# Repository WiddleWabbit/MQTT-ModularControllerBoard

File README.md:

# MQTT Modular Controller Board

*Currently In Testing - Not Yet Tested*

ESP32-S3-WROOM-1U based motherboard designed to communicate externally via MQTT, and read sensors, control interfaces and other hardware through purpose built modules. For example, actuator control (pumps, solenoids, etc.), and water sensor readings etc.

## Features

- ESP32-S3-WROOM-1U microcontroller with antenna support
- Four module slots using standardized 2x10 pin headers
- Power rails: 12 V, 5 V, and 3.3 V supplied to modules
- High-side reverse polarity protection on 12 V and 5 V inputs
- USB-powered operation for programming and testing (no 12 V required)
- Screw terminal power input
- 4-layer PCB designed for assembly (routing / GND / GND / routing)
- 4 x 3.5mm Mounting Holes

## Architecture

### Core Components
- **Microcontroller**: ESP32-S3-WROOM-1U
- **Power Input**: 12 V via screw terminals
- **Power Conversion**:
  - 12 V → 5 V using TPS563200DDCR (TI WEBENCH design)
  - 5 V → 3.3 V using LDO
- **Maximum Outputs**:
  - 12 V: Limited by external supply
  - 5 V: 3 A total (0.8 A used internally)
  - 3.3 V: 1 A total (0.6 A used by ESP32)

### Module Interface
Each of the four modules connects via two 10-pin headers and receives:
- Power: 12 V (4 pins shared), 5 V (2 pins), 3.3 V (2 pins), GND (4 pins)
- Communication:
  - Shared SPI: CS(per module), MOSI(GPIO11), MISO(GPIO13), SCK(GPIO12)
  - Shared I²C: SDA(GPIO4), SCL(GPIO5)
- Control/Detection:
  - One general-purpose GPIO per module
  - One module detection/sense pin per module
  - Module-specific CS pins.

#### Module Slots (Left to Right)
Slot 1:
- General Purpose: GPIO1
- Module Detection: GPIO2
- CS Pin: GPIO16
  
Slot 2:
- General Purpose: GPIO43
- Module Detection: GPIO44
- CS Pin: GPIO15
  
Slot 3:
- General Purpose: GPIO42
- Module Detection: GPIO41
- CS Pin: GPIO7
  
Slot 4:
- General Purpose: GPIO40
- Module Detection: GPIO39
- CS Pin: GPIO6
  
### Additional Features
- USB micro-B for programming and power (VBUS sense on GPIO08)
- Power indicator LED on 3.3 V rail
- EN button and RESET functionality
- Manual download mode: Hold BOOT button while pressing RESET, then release BOOT

### PCB Stackup
4-layer board:  
Component/Routing → Ground plane → Ground plane → Routing

Impedance Control:
Designed for JLCPCB Impedance Control Stackup of JLC04161H-7628, Finished thickness of 1.59mm.

## Setup and Build

**Firmware**: The PlatformIO firmware includes non-blocking WiFi station
reconnection and a captive-portal setup flow. On first boot, the portal scans
nearby networks and offers a selectable SSID list plus manual SSID entry.

**Programming**:
- Connect via USB micro-B.
- Use ESP32 flashing tools (esptool, Arduino IDE, ESP-IDF, etc.).
- For manual bootloader mode: Hold BOOT button, press RESET, release BOOT.

**Module Development**:
Modules must conform to the 2x10 header pinout with 40mm pitch.
Board uses 2 x 10, 8.5mm Female Headers (A2541HWV-10P). Recommended 3A support.

## Repository Contents

- KiCad schematic and PCB files
- Project configuration
- Backups folder

## License

This documentation is part of MQTT-ModularControllerBoard Project and is licensed under the CERN Open Hardware Licence Version 2 - Permissive (CERN-OHL-P-2.0). 
You may redistribute and modify this documentation under the terms of the CERN-OHL-P-2.0. 
This documentation is distributed WITHOUT ANY EXPRESS OR IMPLIED WARRANTY, INCLUDING OF MERCHANTABILITY, SATISFACTORY QUALITY AND FITNESS FOR A PARTICULAR PURPOSE. See the CERN-OHL-P-2.0 for applicable conditions.

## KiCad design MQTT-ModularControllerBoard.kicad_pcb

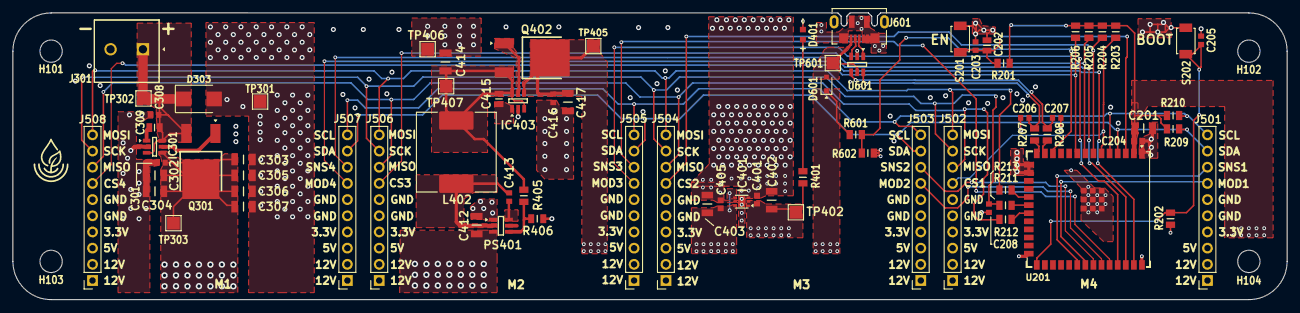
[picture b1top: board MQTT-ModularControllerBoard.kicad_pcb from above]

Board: 4 copper layers, 200.0 x 45.0 mm, 81 parts (0 on the bottom side), 44 nets.

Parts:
C201, C302, C303, C304, C305, C306, C307, C402, C405, C412, C417: 10uF 10% 25V; CAPC3216X180N
C202: 1uF 10% 50V; CAPC2012X135N
C203, C204, C205, C301, C308, C401, C403, C413, C416: 0.1uF 10% 50V; CAPC1608X90N
C206, C207, C208: 22pF 5% 50V; CAPC1608X90N
C309, C415: 220nF 10% 50V; CAPC2012X135N
C414: 47uF 20% 10V; CAPC3216X190N
D303: 13V 21.5V 1uA Leak; DO-214AA_Bidirectional
D401: KT-0603R; LED_0603_1608Metric
D601: 40V 1A; D_SOD-323F
H101, H102, H103, H104: 3.5mm; MountingHole_3.5mm
IC301, IC403: LM74700QDBVTQ1; SOT95P280X145-6N
IC401: TLV76733DRVR; SON65P200X200X80-7N
J301: 1715721
J501, J502, J503, J504, J505, J506, J507, J508: A2541HWV-10P; PinSocket_1x10_P2.54mm_Vertical_Female
J601: 1051640001; CON00906_5_MOL
L402: 10uH, 5.4A, 20%; L_SXN_SMDRI127
PS401: TPS54308DDCR; SOT95P280X110-6N
Q301, Q402: 60V 38A; DPAK__SINGLE-GAUGE__TO-252_369C__ISSUE_F
R201, R202, R203, R204, R205, R206: 10kΩ 1/8W 1%; RESC2013X65N
R207, R208: 22Ω 1/8W 5%; RESC2013X65N
R209, R210: 4.7kΩ 1/8W 1%; RESC2013X65N
R211, R212, R213: 47Ω 1/8W 1%; RESC2013X65N
R401: 330Ω 1/8W 1%; RESC2013X65N
R405, R601, R602: 100kΩ 1/8W 1%; RESC2013X65N
R406: 13.7kΩ 1/8W 1%; RESC2012X60N
S201, S202: Push Button SPST; SW_TS-1088-AR02016
TP301, TP302, TP303, TP402, TP405, TP406, TP407, TP601: TestPoint; TestPoint_Pad_2.0x2.0mm
U201: ESP32-S3-WROOM-1U-N16R8; ESP32-S3-WROOM-1U
U601: ESD Protection IC; SOT95P280X145-6N

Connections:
+3V3: C201.2, C204.1, C401.1, C402.2, IC401.1 (OUT), IC401.2 (SNS), J501.4, J502.4, J503.4, J504.4, J505.4, J506.4, J507.4, J508.4, R201.1, R202.2, R203.2, R204.2, R205.2, R206.2, R209.2, R210.2, R401.2, TP402.1, U201.2 (3V3)
+5V: C403.1, C405.2, C416.2, C417.2, D601.1 (K), IC401.4 (EN), IC401.6 (IN), IC403.4 (CATHODE), J501.3, J502.3, J503.3, J504.3, J505.3, J506.3, J507.3, J508.3, Q402.2 (D), R601.1, TP405.1
+12V: C301.2, C302.2, C303.2, C304.2, C305.2, C306.2, C307.2, C412.2, IC301.4 (CATHODE), J501.1, J501.2, J502.1, J502.2, J503.1, J503.2, J504.1, J504.2, J505.1, J505.2, J506.1, J506.2, J507.1, J507.2, J508.1, J508.2, PS401.3 (VIN), Q301.2 (D), TP303.1
/ESP32-S3/BOOT: C205.1, R202.1, S202.1, U201.27 (GPIO0/BOOT)
/ESP32-S3/CS1: J502.7, R203.1, U201.6 (GPIO6/TOUCH6/ADC1_CH5)
/ESP32-S3/CS2: J504.7, R204.1, U201.7 (GPIO7/TOUCH7/ADC1_CH6)
/ESP32-S3/CS3: J506.7, R205.1, U201.8 (GPIO15/U0RTS/ADC2_CH4/XTAL_32K_P)
/ESP32-S3/CS4: J508.7, R206.1, U201.9 (GPIO16/U0CTS/ADC2_CH5/XTAL_32K_N)
/ESP32-S3/D+: R207.1, U201.14 (GPIO20/U1CTS/ADC2_CH9/CLK_OUT1/USB_D+)
/ESP32-S3/D-: R208.1, U201.13 (GPIO19/U1RTS/ADC2_CH8/CLK_OUT2/USB_D-)
/ESP32-S3/D_R+: C206.2, R207.2, U601.6 (I/O1)
/ESP32-S3/D_R-: C207.2, R208.2, U601.4 (I/O2)
/ESP32-S3/EN: C202.2, C203.1, R201.2, S201.1, U201.3 (EN)
/ESP32-S3/MISO: R212.1, U201.21 (GPIO13/TOUCH13/ADC2_CH2/FSPIQ/FSPIIO7/S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)
/ESP32-S3/MISO_R: J502.8, J504.8, J506.8, J508.8, R212.2
/ESP32-S3/MOD1: J501.7, U201.33 (MTDO/GPIO40/CLK_OUT2)
/ESP32-S3/MOD2: J503.7, U201.35 (MTMS/GPIO42)
/ESP32-S3/MOD3: J505.7, U201.37 (U0TXD/GPIO43/CLK_OUT1)
/ESP32-S3/MOD4: J507.7, U201.39 (GPIO1/TOUCH1/ADC1_CH0)
/ESP32-S3/MOSI: R211.1, U201.19 (GPIO11/TOUCH11/ADC2_CH0/FSPID/FSPIIO5/S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)
/ESP32-S3/MOSI_R: J502.10, J504.10, J506.10, J508.10, R211.2
/ESP32-S3/SCK: R213.1, U201.20 (GPIO12/TOUCH12/ADC2_CH1/FSPICLK/FSPIIO6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)
/ESP32-S3/SCK_R: C208.1, J502.9, J504.9, J506.9, J508.9, R213.2
/ESP32-S3/SCL: J501.10, J503.10, J505.10, J507.10, R210.1, U201.5 (GPIO5/TOUCH5/ADC1_CH4)
/ESP32-S3/SDA: J501.9, J503.9, J505.9, J507.9, R209.1, U201.4 (GPIO4/TOUCH4/ADC1_CH3)
/ESP32-S3/SENSE1: J501.8, U201.32 (MTCK/GPIO39/CLK_OUT3/SUBSPICS1)
/ESP32-S3/SENSE2: J503.8, U201.34 (MTDI/GPIO41/CLK_OUT1)
/ESP32-S3/SENSE3: J505.8, U201.36 (U0RXD/GPIO44/CLK_OUT2)
/ESP32-S3/SENSE4: J507.8, U201.38 (GPIO2/TOUCH2/ADC1_CH1)
/ESP32-S3/VBUS_SNS: R601.2, R602.1, U201.12 (GPIO8/TOUCH8/ADC1_CH7/SUBSPICS1)
/USB Input/D+: J601.3 (D+), U601.1 (I/O1)
/USB Input/D-: J601.2 (D-), U601.3 (I/O2)
GND: C201.1, C202.1, C203.2, C204.2, C205.2, C206.1, C207.1, C208.2, C301.1, C302.1, C303.1, C304.1, C305.1, C306.1, C307.1, C308.2, C401.2, C402.1, C403.2, C405.1, C412.1, C414.1, C416.1, C417.1, D303.2 (A2), D401.1 (K), IC301.2 (GND), IC401.3 (GND_1), IC401.5 (GND_2), IC401.7 (EP), IC403.2 (GND), J301.2, J501.5, J501.6, J502.5, J502.6, J503.5, J503.6, J504.5, J504.6, J505.5, J505.6, J506.5, J506.6, J507.5, J507.6, J508.5, J508.6, J601.4 (ID), J601.5 (GND), J601.6 (GND), PS401.1 (GND), R406.1, R602.2, S201.2, S202.2, TP301.1, TP406.1, U201.1 (GND), U201.15 (GPIO3/TOUCH3/ADC1_CH2), U201.16 (GPIO46), U201.26 (GPIO45), U201.40 (GND), U201.41 (GND), U601.2 (GND)
unnamed: C308.1, C309.1, D303.1 (A1), IC301.3 (EN), IC301.6 (ANODE), J301.1, Q301.3 (S), TP302.1
unnamed: D401.2 (A), R401.1
unnamed: D601.2 (A), J601.1 (VBUS), TP601.1, U601.5 (VBUS)
unnamed: IC301.5 (GATE), Q301.1 (G)
unnamed: C309.2, IC301.1 (VCAP)
unnamed: C414.2, C415.2, IC403.3 (EN), IC403.6 (ANODE), L402.2, Q402.3 (S), R405.2, TP407.1
unnamed: IC403.5 (GATE), Q402.1 (G)
unnamed: C415.1, IC403.1 (VCAP)
unnamed: C413.2, PS401.6 (BOOT)
unnamed: PS401.4 (FB), R405.1, R406.2
unnamed: C413.1, L402.1, PS401.2 (SW)

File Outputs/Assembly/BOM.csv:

"#","Qty","Reference","Value","Manufacturer","Manufacturer Part No","JLCPCB Part #","Package","Footprint"
"1","11","C201,C302,C303,C304,C305,C306,C307,C402,C405,C412,C417","10uF 10% 25V","Samsung Electro-Mechanics","CL31A106KAHNNNE","C9807","1206","JLCPCB Basic:CAPC3216X180N"
"2","1","C202","1uF 10% 50V","Samsung Electro-Mechanics","CL21B105KBFNNNE","C28323","0805","JLCPCB Basic:CAPC2012X135N"
"3","9","C203,C204,C205,C301,C308,C401,C403,C413,C416","0.1uF 10% 50V","YAGEO","CC0603KRX7R9BB104","C14663","0603","JLCPCB Basic:CAPC1608X90N"
"4","1","C208","22pF 5% 50V","Samsung Electro-Mechanics","CL10C220JB8NNNC","C1653","0603","JLCPCB Basic:CAPC1608X90N"
"5","2","C309,C415","220nF 10% 50V","Samsung Electro-Mechanics","CL21B224KBFNNNE","C5378","0805","JLCPCB Basic:CAPC2012X135N"
"6","1","C414","47uF 20% 10V","Samsung Electro-Mechanics","CL31A476MPHNNNE","C96123","1206","JLCPCB Basic:CAPC3216X190N"
"7","1","D303","13V 21.5V 1uA Leak","Littelfuse","SMBJ13CA","C224008","DO-214AA","LITTELFUSE Diodes:DO-214AA_Bidirectional"
"8","1","D401","KT-0603R","Hubei KENTO Elec"," KT-0603R","C2286","0603","JLCPCB Basic:LED_0603_1608Metric"
"9","1","D601","40V 1A","Guangdong Hottech","1N5819WS","C191023","SOD-323","GUANGDONG HOTTECH Diodes:D_SOD-323F"
"10","2","IC301,IC403","LM74700QDBVTQ1","Texas Instruments","LM74700QDBVTQ1","C2653623","SOT-23-6","TEXAS INSTRUMENTS ICs:SOT95P280X145-6N"
"11","1","IC401","TLV76733DRVR","Texas Instruments","TLV76733DRVR","C2848334","WSON-6(2x2)","TEXAS INSTRUMENTS ICs:SON65P200X200X80-7N"
"12","1","J301","1715721"," Phoenix Contact"," 1715721","C480516","Plugin,P=5.08mm","PHOENIX CONTACT Terminals:1715721"
"13","8","J501,J502,J503,J504,J505,J506,J507,J508","A2541HWV-10P","CJT(Changjiang Connectors)","A2541HWV-10P","C225507","Plugin,P=2.54mm","CJT Connectors:PinSocket_1x10_P2.54mm_Vertical_Female"
"14","1","J601","1051640001","MOLEX","1051640001","C234179","SMD","MOLEX Connectors:CON00906_5_MOL"
"15","1","L402","10uH, 5.4A, 20%","SXN(Shun Xiang Nuo Elec)","SMDRI127-100MT","C9904","SMD,12.3x12.3mm","Inductor_SMD:L_SXN_SMDRI127"
"16","1","PS401","TPS54308DDCR","Texas Instruments","TPS54308DDCR","C168839","SOT-23-6","TEXAS INSTRUMENTS ICs:SOT95P280X110-6N"
"17","2","Q301,Q402","60V 38A","onsemi","NVD5C684NLT4G","C236252","DPAK","ONSEMI Transistors:DPAK__SINGLE-GAUGE__TO-252_369C__ISSUE_F"
"18","6","R201,R202,R203,R204,R205,R206","10kΩ 1/8W 1%","UNI-ROYAL(Uniroyal Elec)","0805W8F1002T5E","C17414","0805","JLCPCB Basic:RESC2013X65N"
"19","2","R207,R208","22Ω 1/8W 5%","UNI-ROYAL(Uniroyal Elec)","0805W8F220JT5E","C17561","0805","JLCPCB Basic:RESC2013X65N"
"20","2","R209,R210","4.7kΩ 1/8W 1%","UNI-ROYAL(Uniroyal Elec)","0805W8F4701T5E"," C17673","0805","JLCPCB Basic:RESC2013X65N"
"21","3","R211,R212,R213","47Ω 1/8W 1%","UNI-ROYAL(Uniroyal Elec)","0805W8F470JT5E","C17714","0805","JLCPCB Basic:RESC2013X65N"
"22","1","R401","330Ω 1/8W 1%","UNI-ROYAL(Uniroyal Elec)","0805W8F3300T5E","C17630","0805","JLCPCB Basic:RESC2013X65N"
"23","3","R405,R601,R602","100kΩ 1/8W 1%","UNI-ROYAL(Uniroyal Elec)","0805W8F1003T5E","C149504","0805","JLCPCB Basic:RESC2013X65N"
"24","1","R406","13.7kΩ 1/8W 1%","YAGEO","AC0805FR-0713K7L","C228298","0805","YAGEO Resistors:RESC2012X60N"
"25","2","S201,S202","Push Button SPST","XUNPU","TS-1088-AR02016","C720477","SMD,4x3mm","JLCPCB Basic:SW_TS-1088-AR02016"
"26","1","U201","ESP32-S3-WROOM-1U-N16R8","Espressif Systems","ESP32-S3-WROOM-1U-N16R8","C3013946","SMD,19.2x18mm","ESPRESSIF Microcontrollers:ESP32-S3-WROOM-1U"
"27","1","U601","ESD Protection IC","STMicroelectronics","USBLC6-2SC6","C7519","SOT-23-6L","STMICROELECTRONICS Protection:SOT95P280X145-6N"

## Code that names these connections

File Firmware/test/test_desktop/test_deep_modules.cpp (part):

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  FakeDigitalPin sns2;
  FakeDigitalPin sns3;
  FakeDigitalPin sns4;
  FakeDigitalPin mod1;
  FakeDigitalPin mod2;
  FakeDigitalPin mod3;
  FakeDigitalPin mod4;
  FakeDigitalPin cs1;
  FakeDigitalPin cs2;
  FakeDigitalPin cs3;
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   */
  explicit SlotRig(FakeClock& clockRef)
    : clock(clockRef),
      pins{{sns1, mod1, cs1},
           {sns2, mod2, cs2},
           {sns3, mod3, cs3},
           {sns4, mod4, cs4}}
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   */
  FakeDigitalPin& mod(uint8_t slotIndex)
  {
    FakeDigitalPin* pinsMod[] = {&mod1, &mod2, &mod3, &mod4};
    return *pinsMod[slotIndex];
  }
};
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  TEST_ASSERT_TRUE(rig.programming.active());
  TEST_ASSERT_EQUAL(PinMode::DigitalOutput, board.slots.cs1.mode);
  TEST_ASSERT_TRUE(board.slots.cs1.level);
  TEST_ASSERT_EQUAL(PinMode::DigitalInput, board.slots.mod1.mode);
  for (int i = 0; i < 3; ++i)
  {
    board.bus.update();
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  board.slots.cs1.setMode(PinMode::DigitalOutput);
  board.slots.cs1.write(true);
  const int cs1Writes = board.slots.cs1.writeCount;
  const int mod3Writes = board.slots.mod3.writeCount;
  const PinMode mod3Mode = board.slots.mod3.mode;
  const int mod1Writes = board.slots.mod1.writeCount;

  ProgrammingRig rig(board, 60000, 1000);
  rig.programming.begin(3, ProgrammingMethod::Isp);
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  Board board(kPollMs, kPollMs, kSolenoidSilenceMs, kPollMs, kPumpSilenceMs);
  board.start();
  ProgrammingRig rig(board, 60000, 1000);
  const int mod1Writes = board.slots.mod1.writeCount;
  const int mod2Writes = board.slots.mod2.writeCount;
  const int mod4Writes = board.slots.mod4.writeCount;
  const PinMode mod1Mode = board.slots.mod1.mode;
  const PinMode mod2Mode = board.slots.mod2.mode;
  const PinMode mod4Mode = board.slots.mod4.mode;
  const int cs1Writes = board.slots.cs1.writeCount;
  const int cs2Writes = board.slots.cs2.writeCount;
  rig.programming.begin(2, ProgrammingMethod::Updi);
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  board.start();
  ProgrammingRig quiet(board, 60000, 1000);
  quiet.port.plugged = false;
  const int mod4Writes = board.slots.mod4.writeCount;
  const PinMode mod4Mode = board.slots.mod4.mode;
  quiet.programming.begin(4, ProgrammingMethod::Updi);
  TEST_ASSERT_EQUAL(PinMode::DigitalInputPullup, quiet.mosi.mode);
  TEST_ASSERT_EQUAL(mod4Mode, board.slots.mod4.mode);
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  TEST_ASSERT_FALSE(rig.programming.updiCheckActive());
  TEST_ASSERT_FALSE(rig.programming.active());
  const int cs3Writes = board.slots.cs3.writeCount;
  const int mod1Writes = board.slots.mod1.writeCount;
  const int mod3Writes = board.slots.mod3.writeCount;
  const PinMode mod1Mode = board.slots.mod1.mode;
  const PinMode mod3Mode = board.slots.mod3.mode;

  TEST_ASSERT_TRUE(rig.programming.startUpdiCheck(3));
  TEST_ASSERT_TRUE(rig.programming.updiCheckActive());
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  ProgrammingRig rig(board, 60000, 1000);
  rig.mosi.externalLevel = false;
  const int cs1Writes = board.slots.cs1.writeCount;
  const int mod1Writes = board.slots.mod1.writeCount;
  const PinMode mod1Mode = board.slots.mod1.mode;
  TEST_ASSERT_TRUE(rig.programming.startUpdiCheck(1));
  TEST_ASSERT_EQUAL(PinMode::DigitalOutputOpenDrain, rig.mosi.mode);
  TEST_ASSERT_FALSE(rig.mosi.level);
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  Board board(kPollMs, kPollMs, kSolenoidSilenceMs, kPollMs, kPumpSilenceMs);
  board.start();
  ProgrammingRig rig(board, 60000, 1000);
  const int mod1Writes = board.slots.mod1.writeCount;
  const int mod2Writes = board.slots.mod2.writeCount;
  const PinMode mod1Mode = board.slots.mod1.mode;
  const PinMode mod2Mode = board.slots.mod2.mode;
  TEST_ASSERT_TRUE(rig.programming.startUpdiCheck(1));
  TEST_ASSERT_EQUAL(PinMode::DigitalOutputOpenDrain, rig.mosi.mode);
  TEST_ASSERT_FALSE(rig.mosi.level);
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  TEST_ASSERT_TRUE(wroteLine(serial, "OK programming"));
  TEST_ASSERT_TRUE(wroteLine(
    serial,
    "ISP slot 1: MOSI GPIO11, MISO GPIO13, SCK GPIO12, RESET GPIO6, 3V3, GND"));

  serial.output.clear();
  serial.feed("program 4 updi\n");
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  TEST_ASSERT_EQUAL(4, request.slot);
  TEST_ASSERT_EQUAL(static_cast<int>(ProgrammingMethod::Updi),
                    static_cast<int>(request.method));
  TEST_ASSERT_TRUE(wroteLine(serial, "UPDI slot 4: UPDI GPIO11, 3V3, GND"));

  serial.output.clear();
  serial.feed("program updi\n");
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
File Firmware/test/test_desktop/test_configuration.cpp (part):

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                    static_cast<int>(request.method));
  TEST_ASSERT_EQUAL_STRING("OK programming", slot1.serial.output[0].c_str());
  TEST_ASSERT_EQUAL_STRING(
    "ISP slot 1: MOSI GPIO11, MISO GPIO13, SCK GPIO12, RESET GPIO6, 3V3, GND",
    slot1.serial.output[1].c_str());

  CommandStack slot2;
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  TEST_ASSERT_TRUE(slot2.controller.takeProgrammingRequest(request));
  TEST_ASSERT_EQUAL(2, request.slot);
  TEST_ASSERT_EQUAL_STRING(
    "ISP slot 2: MOSI GPIO11, MISO GPIO13, SCK GPIO12, RESET GPIO7, 3V3, GND",
    slot2.serial.output[1].c_str());

  CommandStack slot3;
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  TEST_ASSERT_TRUE(slot3.controller.takeProgrammingRequest(request));
  TEST_ASSERT_EQUAL(3, request.slot);
  TEST_ASSERT_EQUAL_STRING(
    "ISP slot 3: MOSI GPIO11, MISO GPIO13, SCK GPIO12, RESET GPIO15, 3V3, GND",
    slot3.serial.output[1].c_str());

  CommandStack updi1;
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  TEST_ASSERT_EQUAL(static_cast<int>(ProgrammingMethod::Updi),
                    static_cast<int>(request.method));
  TEST_ASSERT_EQUAL_STRING(
    "UPDI slot 1: UPDI GPIO11, 3V3, GND", updi1.serial.output[1].c_str());

  CommandStack updi4;
  updi4.serial.feed("program 4 updi\n");
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  TEST_ASSERT_TRUE(updi4.controller.takeProgrammingRequest(request));
  TEST_ASSERT_EQUAL(4, request.slot);
  TEST_ASSERT_EQUAL_STRING(
    "UPDI slot 4: UPDI GPIO11, 3V3, GND", updi4.serial.output[1].c_str());
}

/**
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

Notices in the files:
MQTT-ModularControllerBoard.kicad_pcb:
Licensed under CERN-OHL-P v2
